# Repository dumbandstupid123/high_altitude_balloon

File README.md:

// to do 

Sandeep:
- Look into adding the servo to the existing pcb for the flag
- figure out camera

Zane:
- firmware

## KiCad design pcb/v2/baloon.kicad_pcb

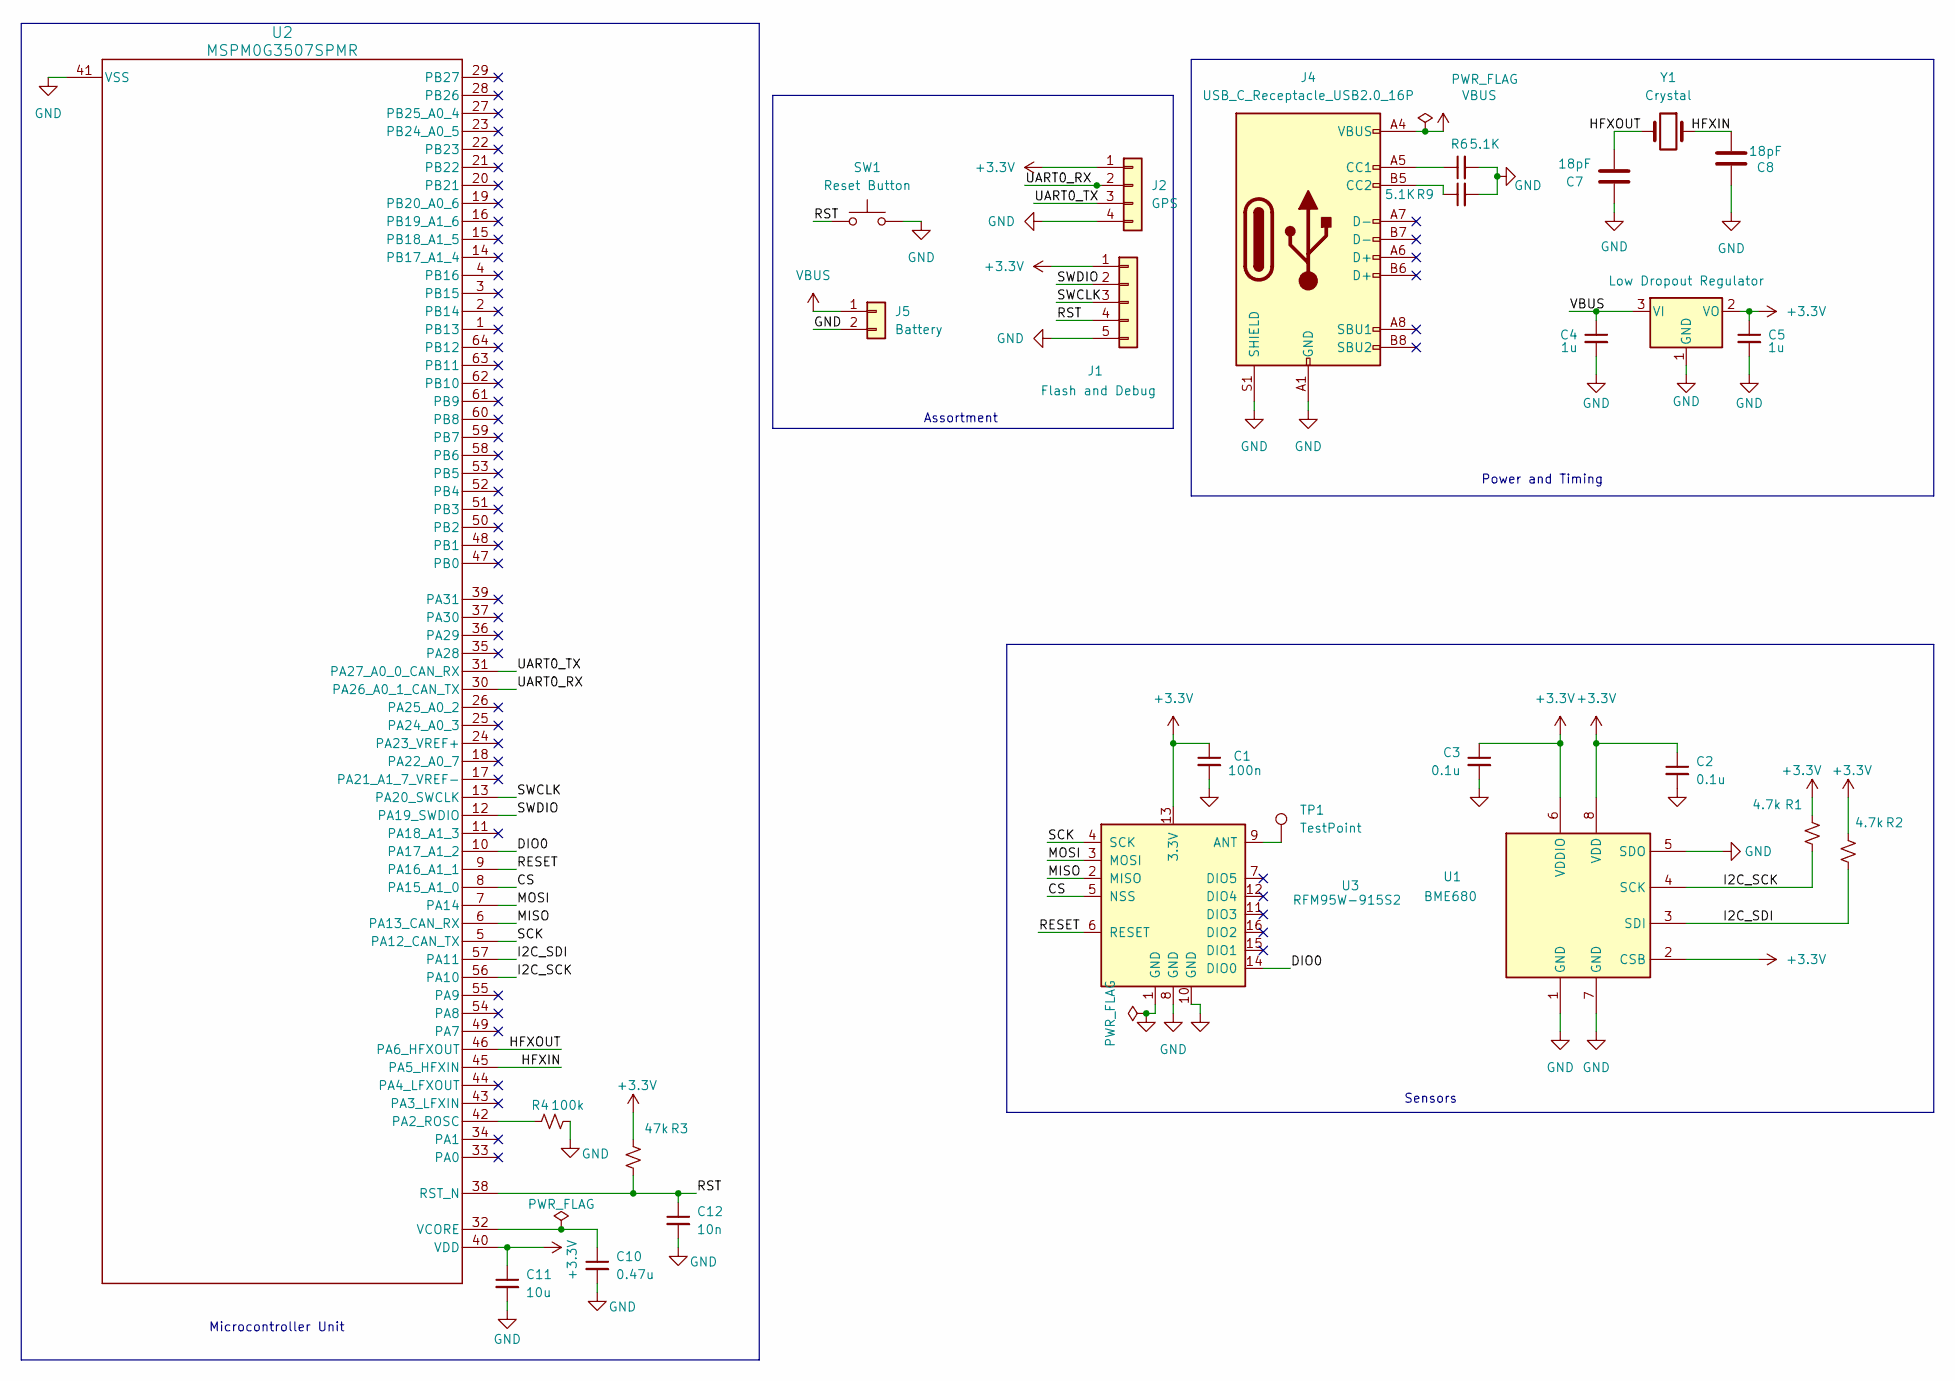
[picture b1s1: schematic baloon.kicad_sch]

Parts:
C1: 100n; C_1206_3216Metric_Pad1.33x1.80mm_HandSolder
C2, C3: 0.1u; C_1206_3216Metric_Pad1.33x1.80mm_HandSolder
C4, C5: 1u; C_1206_3216Metric_Pad1.33x1.80mm_HandSolder
C7, C8: 18pF; C_1206_3216Metric_Pad1.33x1.80mm_HandSolder
C10: 0.47u; C_1206_3216Metric_Pad1.33x1.80mm_HandSolder
C11: 10u; C_1206_3216Metric_Pad1.33x1.80mm_HandSolder
C12: 10n; C_1206_3216Metric_Pad1.33x1.80mm_HandSolder
J1: Flash and Debug; PinHeader_1x05_P2.54mm_Vertical
J2: GPS; PinHeader_1x04_P2.54mm_Vertical
J4: USB_C_Receptacle_USB2.0_16P; USB_C_Receptacle_HRO_TYPE-C-31-M-12
J5: Battery; PinHeader_1x02_P2.54mm_Vertical
R1, R2: 4.7k; R_1206_3216Metric_Pad1.30x1.75mm_HandSolder
R3: 47k; R_1206_3216Metric_Pad1.30x1.75mm_HandSolder
R4: 100k; R_1206_3216Metric_Pad1.30x1.75mm_HandSolder
R6, R9: 5.1K; R_1206_3216Metric_Pad1.30x1.75mm_HandSolder
SW1: Reset Button; SW_SPST_TL3342
TP1: TestPoint; TestPoint_Pad_D2.0mm
U1: BME680; Bosch_LGA-8_3x3mm_P0.8mm_ClockwisePinNumbering
U2: MSPM0G3507SPMR; LQFP-64_10x10mm_P0.5mm
U3: RFM95W-915S2; HOPERF_RFM9XW_SMD
U4: Low Dropout Regulator; SOT-23-3
Y1: Crystal; Crystal_SMD_3225-4Pin_3.2x2.5mm

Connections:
+3.3V: C1.1, C2.1, C3.1, C5.1, C11.1, J1.1, J2.1, R1.2, R2.2, R3.2, U1.2 (CSB), U1.6 (VDDIO), U1.8 (VDD), U2.40 (VDD), U3.13 (3.3V), U4.2 (VO)
/CS: U2.8 (PA15_A1_0), U3.5 (NSS)
/DIO0: U2.10 (PA17_A1_2), U3.14 (DIO0)
/HFXIN: C8.2, U2.45 (PA5_HFXIN), Y1.1
/HFXOUT: C7.2, U2.46 (PA6_HFXOUT), Y1.2
/I2C_SCK: R1.1, U1.4 (SCK), U2.56 (PA10)
/I2C_SDI: R2.1, U1.3 (SDI), U2.57 (PA11)
/MISO: U2.6 (PA13_CAN_RX), U3.2 (MISO)
/MOSI: U2.7 (PA14), U3.3 (MOSI)
/RESET: U2.9 (PA16_A1_1), U3.6 (RESET)
/RST: C12.1, J1.4, R3.1, SW1.1, U2.38 (RST_N)
/SCK: U2.5 (PA12_CAN_TX), U3.4 (SCK)
/SWCLK: J1.3, U2.13 (PA20_SWCLK)
/SWDIO: J1.2, U2.12 (PA19_SWDIO)
/UART0_RX: J2.2, U2.30 (PA26_A0_1_CAN_TX)
/UART0_TX: J2.3, U2.31 (PA27_A0_0_CAN_RX)
GND: C1.2, C2.2, C3.2, C4.2, C5.2, C7.1, C8.1, C10.2, C11.2, C12.2, J1.5, J2.4, J4.A1 (GND), J4.A12 (GND), J4.B1 (GND), J4.B12 (GND), J4.S1 (SHIELD), J5.2, R4.2, R6.2, R9.2, SW1.2, U1.1 (GND), U1.5 (SDO), U1.7 (GND), U2.41 (VSS), U3.1 (GND), U3.8 (GND), U3.10 (GND), U4.1 (GND)
unnamed: J4.A5 (CC1), R6.1
unnamed: J4.B5 (CC2), R9.1
unnamed: R4.1, U2.42 (PA2_ROSC)
unnamed: C10.1, U2.32 (VCORE)
unnamed: TP1.1, U3.9 (ANT)
VBUS: C4.1, J4.A4 (VBUS), J4.A9 (VBUS), J4.B4 (VBUS), J4.B9 (VBUS), J5.1, U4.3 (VI)

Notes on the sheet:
Assortment
Sensors
Power and Timing
Microcontroller Unit

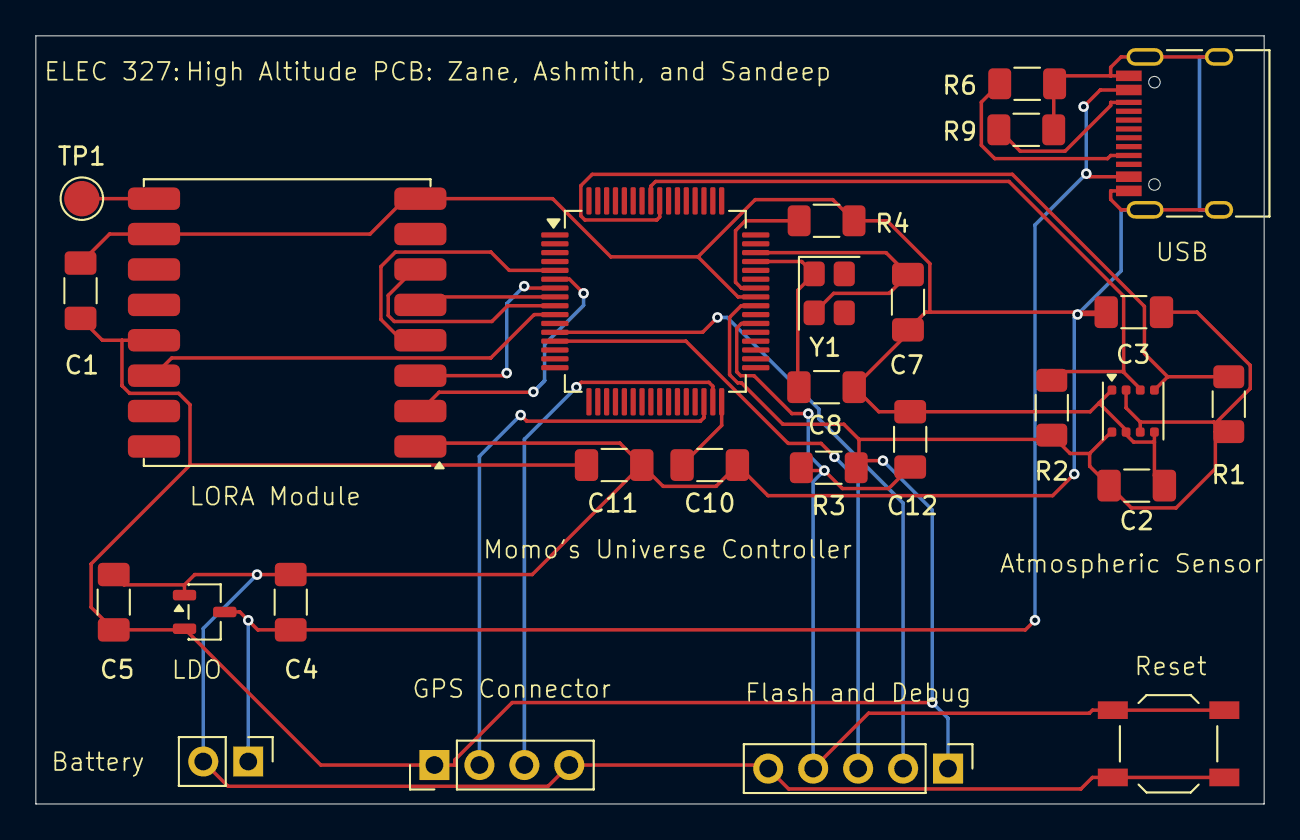
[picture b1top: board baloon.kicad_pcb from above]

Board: 2 copper layers, 69.4 x 43.4 mm, 27 parts (0 on the bottom side), 23 nets.

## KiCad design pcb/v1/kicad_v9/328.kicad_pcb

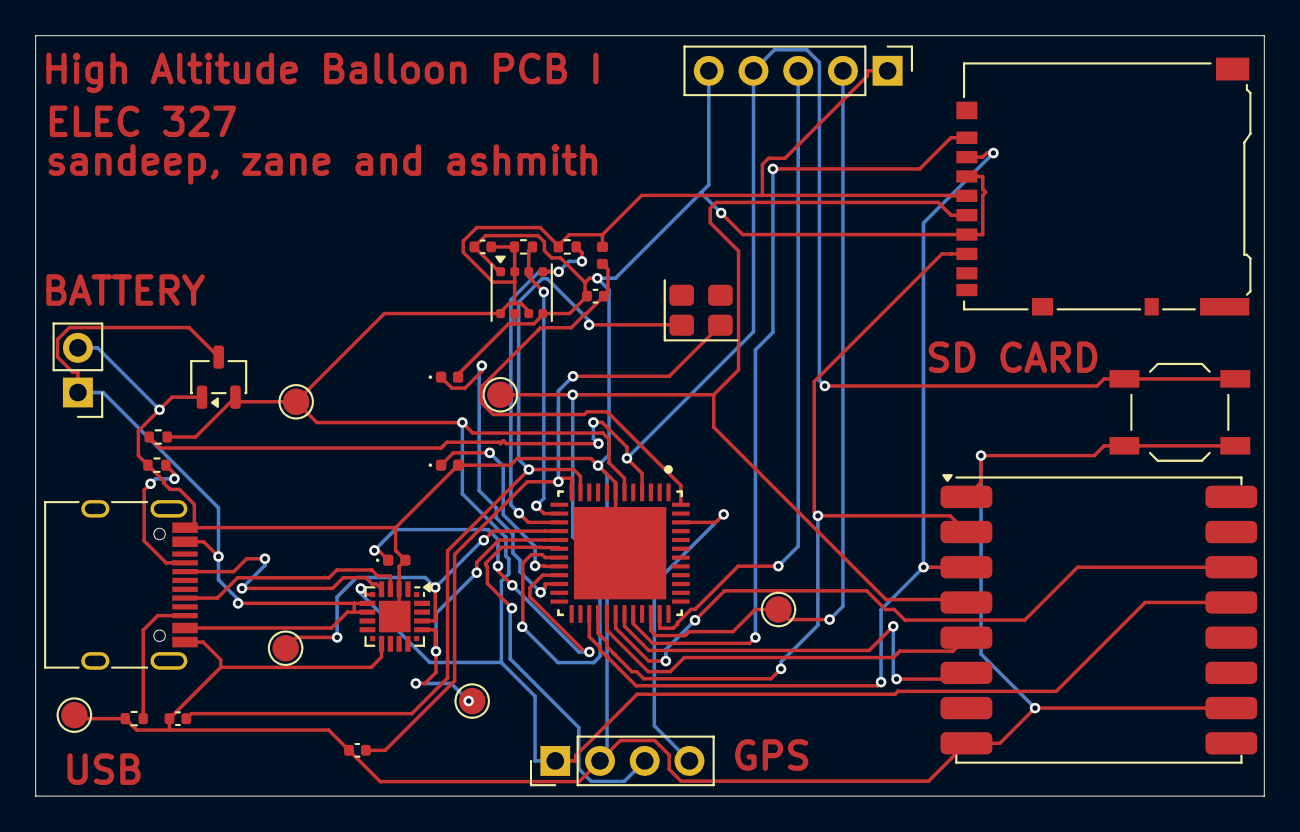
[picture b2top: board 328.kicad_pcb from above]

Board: 2 copper layers, 69.8 x 43.2 mm, 31 parts (0 on the bottom side), 29 nets.

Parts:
C7, C8: 18pF; C_0402_1005Metric
C9, C11: 100nF; C_0402_1005Metric
D1: POWER; LED_0402_1005Metric
D2: LED; LED_0402_1005Metric
D3: LORA; LED_0402_1005Metric
J1: USB C; USB_C_Receptacle_HRO_TYPE-C-31-M-12
J2: CONNECTS TO GPS; PinHeader_1x04_P2.54mm_Vertical
J3: Battery Connection; PinHeader_1x02_P2.54mm_Vertical
J5: Conn_01x05; PinHeader_1x05_P2.54mm_Vertical
J6: SD Card; microSD_HC_Hirose_DM3AT-SF-PEJM5
L1: L; L_0402_1005Metric
R4, R5: 4.7k; R_0402_1005Metric
R6: 10k; R_0402_1005Metric
R7, R8: 5.1k; R_0402_1005Metric
SW1: SW_Push; SW_SPST_TL3342
TP1, TP2, TP3, TP4, TP5, TP6: TestPoint; TestPoint_Pad_D1.5mm
U1: MSP MCU; RGZ0048A-IPC_A
U2: USB TO UART; SiliconLabs_QFN-20-1EP_3x3mm_P0.5mm_EP1.8x1.8mm
U3: Low Dropout Regulator; SOT-23-3
U4: RFM95W-915S2; HOPERF_RFM9XW_SMD
U5: BME680; Bosch_LGA-8_3x3mm_P0.8mm_ClockwisePinNumbering
Y1: Crystal; Crystal_SMD_3225-4Pin_3.2x2.5mm

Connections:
+3.3V: C9.1, J2.1, J5.1, J6.4 (VDD), L1.2, R4.1, R5.1, R6.2, TP1.1, U1.6 (VDD), U2.6 (VDD), U3.2 (VO), U4.13 (3.3V), U5.2 (CSB), U5.6 (VDDIO), U5.8 (VDD)
/HFXIN: C8.2, U1.11 (PA5_HFXIN_FCC_IN), Y1.1
/HFXOUT: C7.2, U1.12 (PA6_HFCLK_IN_HFXOUT), Y1.2
/I2C_SCL: R4.2, U1.15 (PB3), U5.4 (SCK)
/I2C_SDA: R5.2, U1.14 (PB2), U5.3 (SDI)
/LED-PWR: D1.1 (K), U1.20 (PB6)
/LED_GPS: D2.1 (K), U1.21 (PB7)
/LED_LORA: D3.1 (K), U1.22 (PB8)
/LORA_CS: U1.29 (PA14_CLK_OUT_A0_12), U4.5 (NSS)
/LORA_IRQ: U1.30 (PA15_A1_0), U4.14 (DIO0)
/LORA_RST: U1.31 (PA16_A1_1_FCC_IN), U4.6 (RESET)
/RESET: J5.4, R6.1, SW1.1, U1.4 (RST_N)
/SD_CS: J6.1 (CD/DAT3), U1.32 (PA17_A1_2)
/SPIO_CLK: J6.5 (CLK), TP5.1, U1.19 (PA11), U4.4 (SCK)
/SPIO_MISO: J6.7 (DAT0), U1.28 (PA13), U4.2 (MISO)
/SPIO_MOSI: J6.2 (CMD), U1.27 (PA12_FCC_IN), U4.3 (MOSI)
/SWCLK: J5.3, U1.35 (PA20_SWCLK)
/SWDIO: J5.2, TP6.1, U1.34 (PA19_SWDIO)
/UART0_RX: TP4.1, U1.17 (PA9_RTC_OUT_CLK_OUT), U2.17 (RXD)
/UART0_TX: TP3.1, U1.16 (PA8), U2.18 (TXD)
/UART1_RX: J2.3, U1.18 (PA10_CLK_OUT)
/UART1_TX: J2.4, U1.46 (PA26_A0_1)
/USB_DM: J1.B7 (D-), U2.5 (D-)
/USB_DP: J1.B6 (D+), U2.4 (D+)
/VBUS: J1.A4 (VBUS), J1.A9 (VBUS), J1.B4 (VBUS), J1.B9 (VBUS), J3.1, U2.7 (VREGIN), U2.8 (VBUS), U3.3 (VI)
GND: C7.1, C8.1, C9.2, C11.2, D1.2 (A), D2.2 (A), D3.2 (A), J1.A1 (GND), J1.A12 (GND), J1.B1 (GND), J1.B12 (GND), J2.2, J3.2, J5.5, J6.3 (VSS), J6.6 (VSS), R7.2, R8.2, SW1.2, TP2.1, U1.7 (VSS), U1.49 (Thermal_pad), U2.3 (GND), U2.12 (GND), U2.21 (GND), U3.1 (GND), U4.1 (GND), U4.8 (GND), U4.10 (GND), U5.1 (GND), U5.5 (SDO), U5.7 (GND)
unnamed: J1.A5 (CC1), R8.1
unnamed: J1.B5 (CC2), R7.1
unnamed: C11.1, L1.1, U1.48 (VCORE)

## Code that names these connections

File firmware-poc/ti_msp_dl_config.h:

/*
 * LaunchPad proof-of-concept configuration for LP-MSPM0G3507.
 * This file mirrors what SysConfig should generate from launchpad_poc.syscfg.
 */
#ifndef ti_msp_dl_config_h
#define ti_msp_dl_config_h

#define CONFIG_LP_MSPM0G3507
#define CONFIG_MSPM0G3507

#if defined(__ti_version__) || defined(__TI_COMPILER_VERSION__)
#define SYSCONFIG_WEAK __attribute__((weak))
#elif defined(__IAR_SYSTEMS_ICC__)
#define SYSCONFIG_WEAK __weak
#elif defined(__GNUC__)
#define SYSCONFIG_WEAK __attribute__((weak))
#endif

#include <stdbool.h>

#include <ti/devices/msp/msp.h>
#include <ti/driverlib/driverlib.h>
#include <ti/driverlib/m0p/dl_core.h>

#ifdef __cplusplus
extern "C" {
#endif

#define POWER_STARTUP_DELAY (16U)
#define CPUCLK_FREQ         (32000000U)

/* Debug UART over the XDS110 backchannel path on PA10/PA11. */
#define UART_DEBUG_INST                 UART0
#define UART_DEBUG_INST_FREQUENCY       32000000U
#define GPIO_UART_DEBUG_RX_PORT         GPIOA
#define GPIO_UART_DEBUG_TX_PORT         GPIOA
#define GPIO_UART_DEBUG_RX_PIN          DL_GPIO_PIN_11
#define GPIO_UART_DEBUG_TX_PIN          DL_GPIO_PIN_10
#define GPIO_UART_DEBUG_IOMUX_RX        (IOMUX_PINCM22)
#define GPIO_UART_DEBUG_IOMUX_TX        (IOMUX_PINCM21)
#define GPIO_UART_DEBUG_IOMUX_RX_FUNC   IOMUX_PINCM22_PF_UART0_RX
#define GPIO_UART_DEBUG_IOMUX_TX_FUNC   IOMUX_PINCM21_PF_UART0_TX
#define UART_DEBUG_BAUD_RATE            (115200U)
#define UART_DEBUG_IBRD_32_MHZ_115200_BAUD (17U)
#define UART_DEBUG_FBRD_32_MHZ_115200_BAUD (23U)

/* LaunchPad-valid hardware I2C mapping for BME680 tests. */
#define I2C_ENV_INST                  I2C1
#define I2C_ENV_BUS_SPEED_HZ         (400000U)
#define GPIO_I2C_ENV_SDA_PORT        GPIOB
#define GPIO_I2C_ENV_SDA_PIN         DL_GPIO_PIN_3
#define GPIO_I2C_ENV_IOMUX_SDA       (IOMUX_PINCM16)
#define GPIO_I2C_ENV_IOMUX_SDA_FUNC  IOMUX_PINCM16_PF_I2C1_SDA
#define GPIO_I2C_ENV_SCL_PORT        GPIOB
#define GPIO_I2C_ENV_SCL_PIN         DL_GPIO_PIN_2
#define GPIO_I2C_ENV_IOMUX_SCL       (IOMUX_PINCM15)
#define GPIO_I2C_ENV_IOMUX_SCL_FUNC  IOMUX_PINCM15_PF_I2C1_SCL

/* Shared SPI bus for LoRa + microSD on LaunchPad pins. */
#define SPI_SHARED_INST                SPI1
#define GPIO_SPI_SHARED_PICO_PORT      GPIOB
#define GPIO_SPI_SHARED_PICO_PIN       DL_GPIO_PIN_8
#define GPIO_SPI_SHARED_IOMUX_PICO     (IOMUX_PINCM25)
#define GPIO_SPI_SHARED_IOMUX_PICO_FUNC IOMUX_PINCM25_PF_SPI1_PICO
#define GPIO_SPI_SHARED_POCI_PORT      GPIOB
#define GPIO_SPI_SHARED_POCI_PIN       DL_GPIO_PIN_7
#define GPIO_SPI_SHARED_IOMUX_POCI     (IOMUX_PINCM24)
#define GPIO_SPI_SHARED_IOMUX_POCI_FUNC IOMUX_PINCM24_PF_SPI1_POCI
#define GPIO_SPI_SHARED_SCLK_PORT      GPIOB
#define GPIO_SPI_SHARED_SCLK_PIN       DL_GPIO_PIN_9
#define GPIO_SPI_SHARED_IOMUX_SCLK     (IOMUX_PINCM26)
#define GPIO_SPI_SHARED_IOMUX_SCLK_FUNC IOMUX_PINCM26_PF_SPI1_SCLK

/* Manual chip-select and radio control pins. */
#define GPIO_LORA_PORT                GPIOB
#define GPIO_LORA_CS_PIN              DL_GPIO_PIN_6
#define GPIO_LORA_CS_IOMUX            (IOMUX_PINCM23)
#define GPIO_LORA_RST_PIN             DL_GPIO_PIN_0
#define GPIO_LORA_RST_IOMUX           (IOMUX_PINCM12)
#define GPIO_LORA_DIO0_PIN            DL_GPIO_PIN_15
#define GPIO_LORA_DIO0_IOMUX          (IOMUX_PINCM32)

#define GPIO_SD_PORT                  GPIOB
#define GPIO_SD_CS_PIN                DL_GPIO_PIN_17
#define GPIO_SD_CS_IOMUX              (IOMUX_PINCM43)

void SYSCFG_DL_init(void);
void SYSCFG_DL_initPower(void);
void SYSCFG_DL_GPIO_init(void);
void SYSCFG_DL_SYSCTL_init(void);
void SYSCFG_DL_UART_DEBUG_init(void);
void SYSCFG_DL_I2C_ENV_init(void);
void SYSCFG_DL_SPI_SHARED_init(void);
bool SYSCFG_DL_saveConfiguration(void);
bool SYSCFG_DL_restoreConfiguration(void);

#ifdef __cplusplus
}
#endif

#endif

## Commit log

2026-03-09 initial schematic - parts placement done
2026-03-09 real schematic with all components placed
2026-03-10 Complete schematic - ERC 0 errors
2026-03-12 datasheet for LORA stuff
2026-03-21 Add files via upload
    new complete pcb with corrected power regulation anf connections
2026-03-25 Create blank
    folder for datasheets
2026-03-25 Rename LORA_datasheet.pdf to datasheets/LORA_datasheet.pdf
2026-03-25 Create blank
2026-03-25 Rename 328.kicad_pcb to pcb/v1/328.kicad_pcb
2026-03-25 Rename 328.kicad_pro to pcb/v1/328.kicad_pro
2026-03-25 Rename 328.kicad_sch to pcb/v1/328.kicad_sch
2026-03-25 Rename Schematic_connections.pdf to system_design/Schematic_connections.pdf
2026-03-25 Add initial project tasks to README
2026-03-25 Add vendored BME68x driver and FatFs sources
2026-03-26 Add portable types, GPS parser, telemetry math, CSV protocol, and mission app
2026-03-26 Add CMake host build, platform stub, and top-level firmware readme
2026-03-27 Add BME680, SX1276 LoRa, and FatFs SD logging modules
2026-03-28 Add MSPM0 platform layer and disk I/O for CCS (v1 software buses)
2026-03-29 Add Code Composer project, SysConfig, and generated MSPM0 config:
2026-03-31 cleanup
2026-03-31 Add LaunchPad firmware PoC for I2C, LoRa, and microSD testing
    Create a new firmware-poc CCS project for the LP-MSPM0G3507 that reuses the existing BME680, SX1276, and FatFs code where practical. Add LaunchPad-specific setup, bench-test flows, and documentation 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
2026-03-31 update ccs build
2026-03-31 remove bme from poc
2026-04-08 poc testing different modes for lora, bme, and sd card reader
2026-04-17 pcb updates
2026-04-25 kicad v9 updates
2026-04-25 kicad
2026-04-29 Add PCB v2 KiCad project files and gerbers
